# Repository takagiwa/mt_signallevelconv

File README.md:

# mt_signallevelconv

based on EDN article https://www.edn.com/ltc-design-note-robust-10mhz-reference-clock-input-protection-circuit-and-distributor-for-rf-systems/

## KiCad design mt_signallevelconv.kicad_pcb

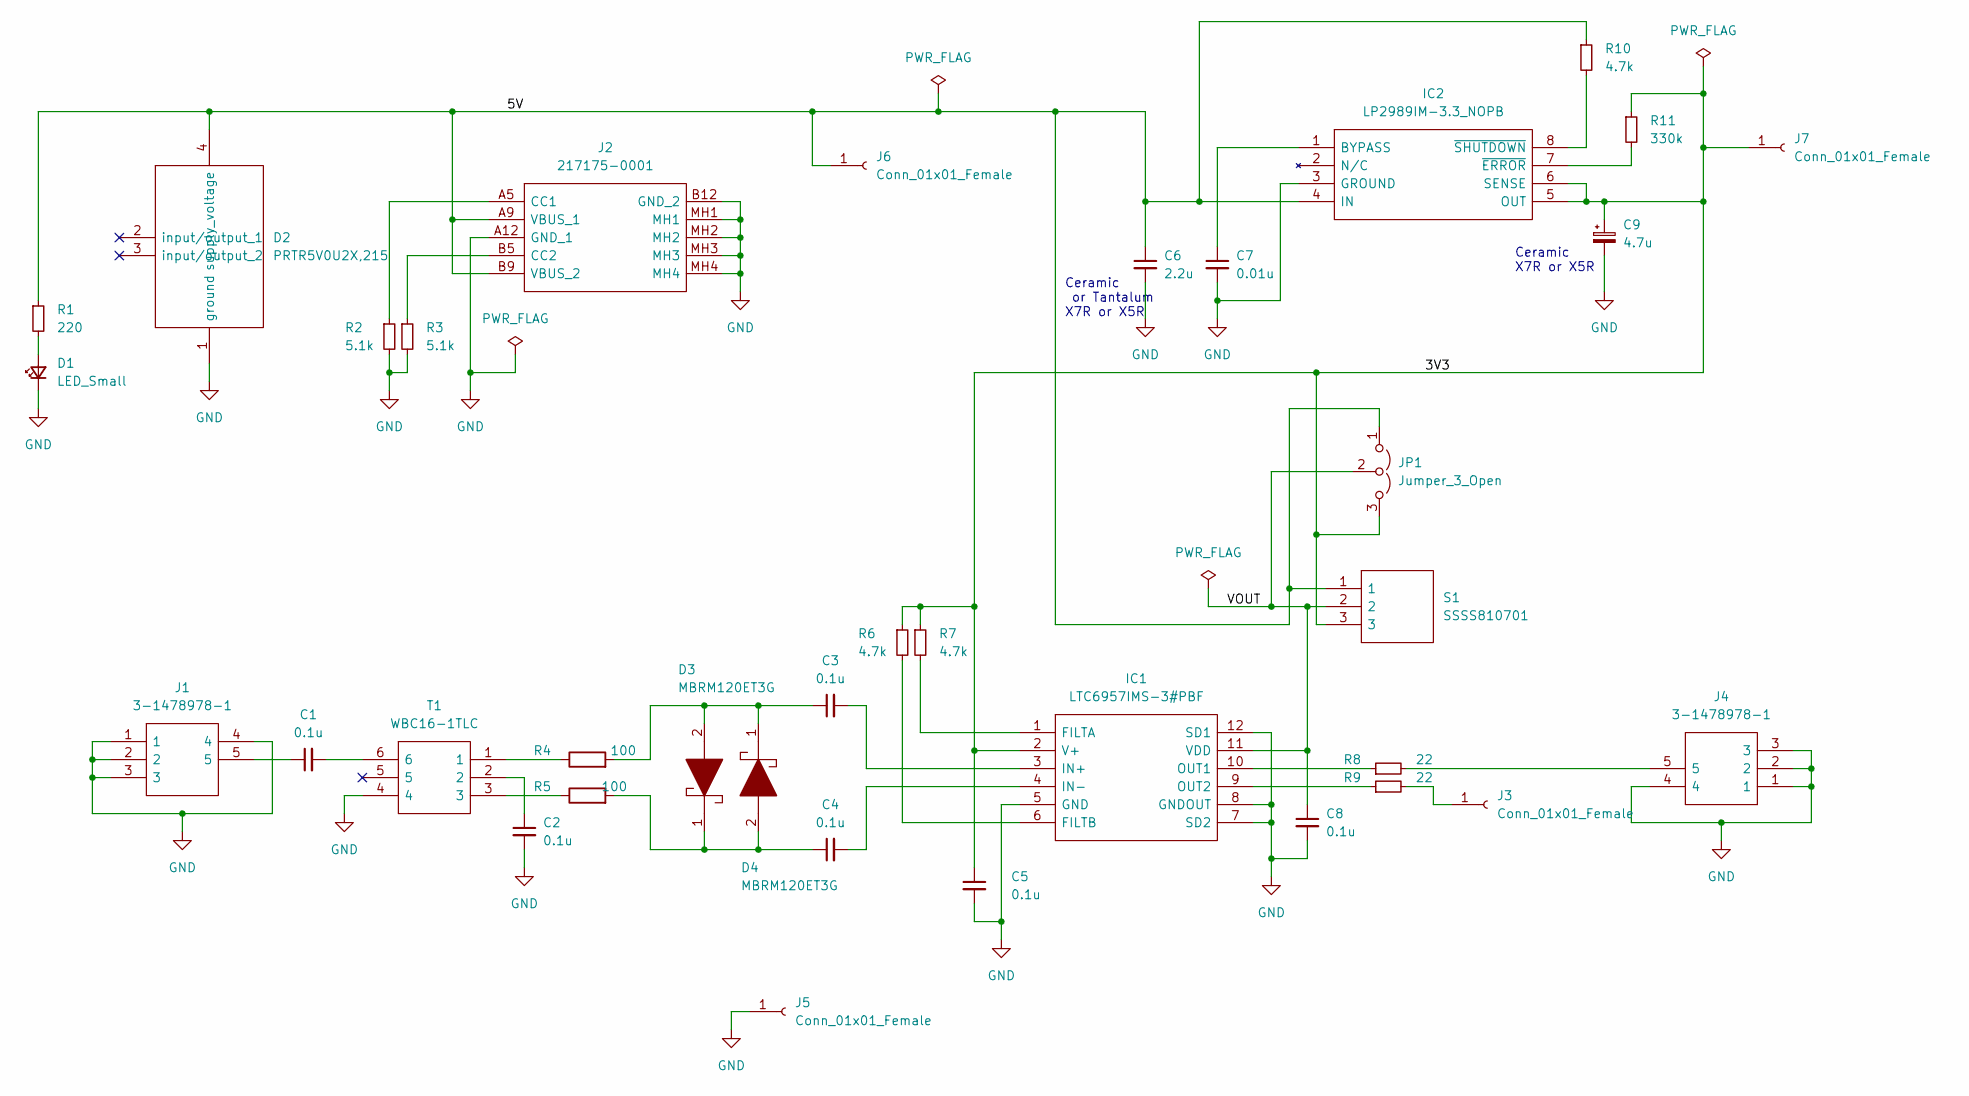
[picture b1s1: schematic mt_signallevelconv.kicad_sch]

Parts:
C1, C2, C3, C4, C5, C8: 0.1u; C_0805_2012Metric_Pad1.18x1.45mm_HandSolder
C6: 2.2u; C_0805_2012Metric_Pad1.18x1.45mm_HandSolder
C7: 0.01u; C_0805_2012Metric_Pad1.18x1.45mm_HandSolder
C9: 4.7u; C_0805_2012Metric_Pad1.18x1.45mm_HandSolder
D1: LED_Small; LED_0805_2012Metric_Pad1.15x1.40mm_HandSolder
D2: PRTR5V0U2X,215; PRTR5V0U2X; Mouser Part Number 771-PRTR5V0U2X-T/R
D3, D4: MBRM120ET3G; Mouser Part Number 863-MBRM120ET3G
IC1: LTC6957IMS-3#PBF; SOP65P490X110-12N; Manufacturer_Part_Number LTC6957IMS-3#PBF
IC2: LP2989IM-3.3_NOPB; SOIC127P600X175-8N; Mouser Part Number 926-2989IM-3.3/NOPB
J1, J4: 3-1478978-1; Mouser Part Number 571-3-1478978-1
J2: 217175-0001; 2171750001; Mouser Part Number 538-217175-0001
J3, J5, J6, J7: Conn_01x01_Female; PinSocket_1x01_P2.54mm_Vertical
JP1: Jumper_3_Open; SolderJumper-3_P2.0mm_Open_TrianglePad1.0x1.5mm
R1: 220; R_0805_2012Metric_Pad1.20x1.40mm_HandSolder
R2, R3: 5.1k; R_0805_2012Metric_Pad1.20x1.40mm_HandSolder
R4, R5: 100; R_0805_2012Metric_Pad1.20x1.40mm_HandSolder
R6, R7, R10: 4.7k; R_0805_2012Metric_Pad1.20x1.40mm_HandSolder
R8, R9: 22; R_0805_2012Metric_Pad1.20x1.40mm_HandSolder
R11: 330k; R_0805_2012Metric_Pad1.20x1.40mm_HandSolder
S1: SSSS810701; Mouser Part Number 688-SSSS810701
T1: WBC16-1TLC; WBC161TLC; Mouser Part Number 994-WBC16-1TLC

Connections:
/3V3: C5.1, C9.1, IC1.2 (V+), IC2.5 (OUT), IC2.6 (SENSE), J7.1, JP1.3 (B), R6.1, R7.1, R11.1, S1.3
/5V: C6.1, D2.4 (supply_voltage), IC2.4 (IN), J2.A9 (VBUS_1), J2.B9 (VBUS_2), J6.1, JP1.1 (A), R1.1, R10.1, S1.1
/VOUT: C8.1, IC1.11 (VDD), JP1.2 (C), S1.2
GND: C2.2, C5.2, C6.2, C7.2, C8.2, C9.2, D1.1 (K), D2.1 (ground), IC1.5 (GND), IC1.7 (SD2), IC1.8 (GNDOUT), IC1.12 (SD1), IC2.3 (GROUND), J1.1, J1.2, J1.3, J1.4, J2.A12 (GND_1), J2.B12 (GND_2), J2.MH1, J2.MH2, J2.MH3, J2.MH4, J4.1, J4.2, J4.3, J4.4, J5.1, R2.2, R3.2, T1.4
unnamed: C1.1, J1.5
unnamed: C1.2, T1.6
unnamed: C2.1, T1.2
unnamed: C3.1, D3.2, D4.1, R4.2
unnamed: C3.2, IC1.3 (IN+)
unnamed: C4.1, D3.1, D4.2, R5.2
unnamed: C4.2, IC1.4 (IN-)
unnamed: C7.1, IC2.1 (BYPASS)
unnamed: D1.2 (A), R1.2
unnamed: IC1.1 (FILTA), R7.2
unnamed: IC1.6 (FILTB), R6.2
unnamed: IC1.9 (OUT2), R9.1
unnamed: IC1.10 (OUT1), R8.1
unnamed: IC2.7 (~ERROR), R11.2
unnamed: IC2.8 (~SHUTDOWN), R10.2
unnamed: J2.A5 (CC1), R2.1
unnamed: J2.B5 (CC2), R3.1
unnamed: J3.1, R9.2
unnamed: J4.5, R8.2
unnamed: R4.1, T1.1
unnamed: R5.1, T1.3

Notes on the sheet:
Ceramic or Tantalum X7R or X5R
Ceramic X7R or X5R

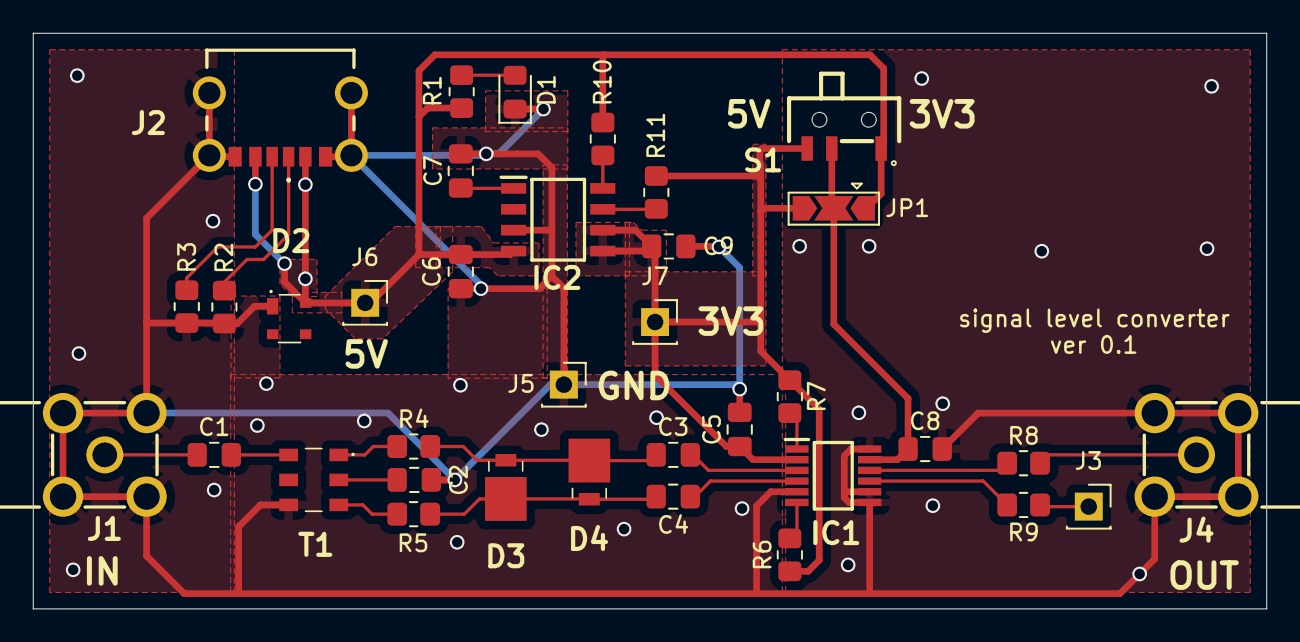
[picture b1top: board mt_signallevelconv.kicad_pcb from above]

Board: 2 copper layers, 75.0 x 35.0 mm, 36 parts (0 on the bottom side), 25 nets.

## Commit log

2022-02-06 first
